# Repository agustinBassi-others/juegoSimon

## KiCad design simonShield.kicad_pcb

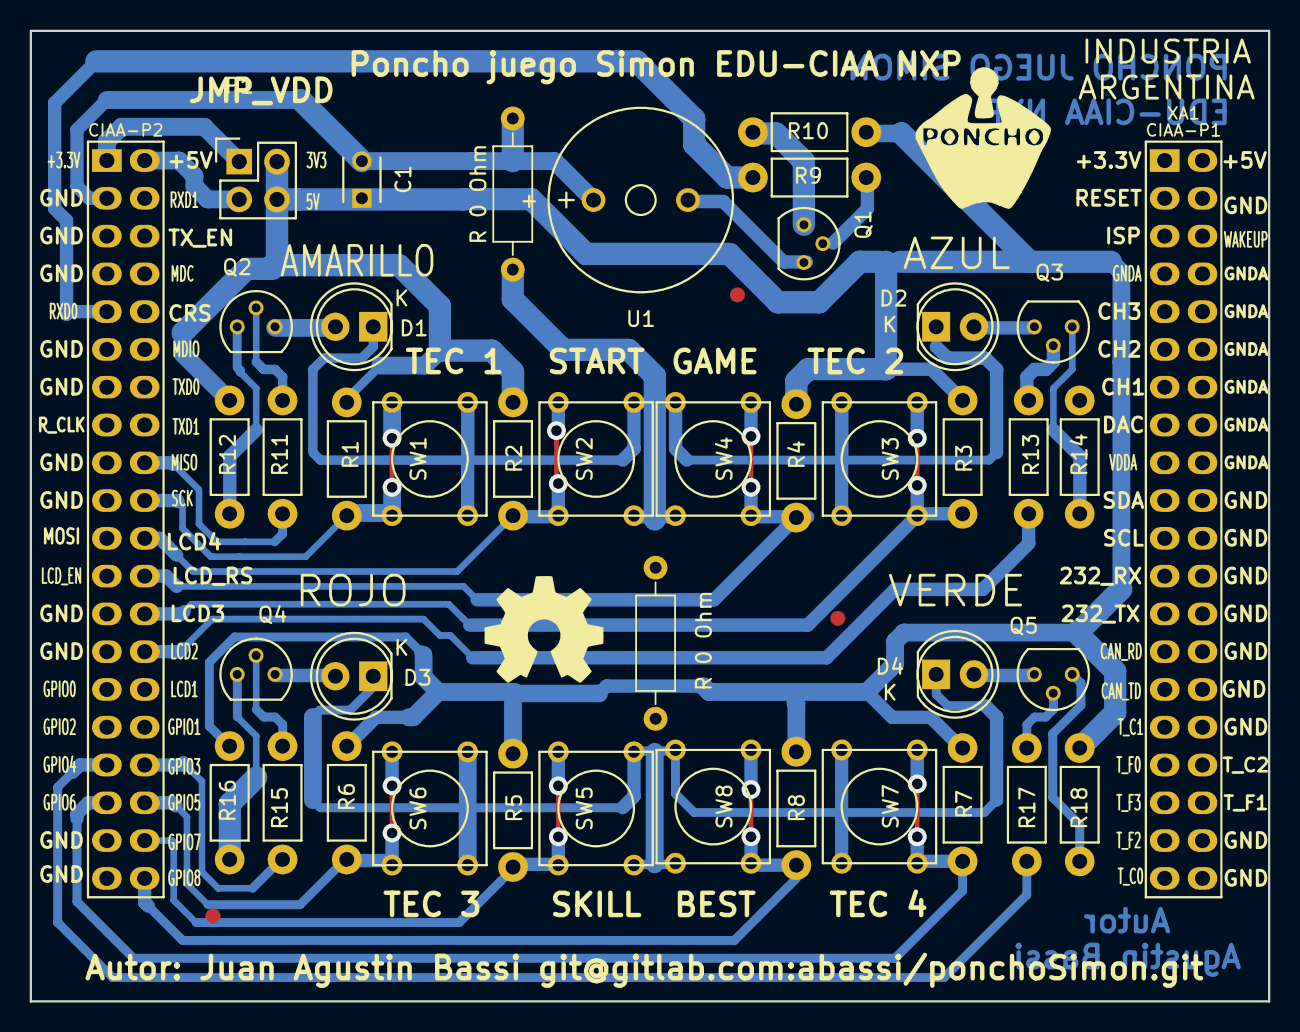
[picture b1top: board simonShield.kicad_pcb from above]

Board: 2 copper layers, 83.2 x 65.2 mm, 45 parts (0 on the bottom side), 32 nets.

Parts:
C1: C_100nF; C_Disc_D3_P2.5
D1: AMARILLO; LED-5MM
D2: AZUL; LED-5MM
D3: ROJO; LED-5MM
D4: VERDE; LED-5MM
F1, F2, F3: FIDUCIAL; Fiducial_1mm
G101: Logo_OSHWA
P1: PWR_JUMPER; Pin_Header_Straight_2x02
Q1, Q2, Q3, Q4, Q5: BC547; TO-92_Molded_Narrow
R1, R2, R3, R4, R5, R6, R7, R8, R9: 3K3; Resistor_Horizontal_RM7mm
R10: 1K; Resistor_Horizontal_RM7mm
R11, R13, R15, R17: 10K; Resistor_Horizontal_RM7mm
R12, R14, R16, R18: 680; Resistor_Horizontal_RM7mm
R 0 Ohm, R 0 Ohm#2: R; R_Axial_DIN0207_L6.3mm_D2.5mm_P10.16mm_Horizontal
SW1, SW2, SW3, SW4, SW5, SW6, SW7, SW8: SW_PUSH; SW_PUSH_SMALL
U1: BUZZER; MagneticBuzzer_ProSignal_ABT-410-RC
XA1: Conn_Poncho2P_2x_20x2; Conn_Poncho_SinBorde

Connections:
/buttons/BTN_CFG_1: R2.1, SW2.1, XA1.62
/buttons/BTN_CFG_2: R4.1, SW4.1, XA1.64
/buttons/BTN_CFG_3: R6.1, SW6.1, XA1.76
/buttons/BTN_CFG_4: R8.1, SW8.1, XA1.80
/buttons/BTN_LED_1: R1.1, SW1.1, XA1.60
/buttons/BTN_LED_2: R3.1, SW3.1, XA1.66
/buttons/BTN_LED_3: R5.1, SW5.1, XA1.78
/buttons/BTN_LED_4: R7.1, SW7.1, XA1.75
/ciaaConector/LED_1: R11.1, XA1.58
/ciaaConector/LED_2: R13.1, XA1.68
/ciaaConector/LED_3: R15.1, XA1.74
/ciaaConector/LED_4: R17.1, XA1.73
/ciaaConector/PWM: R9.2, XA1.49
GND: C1.2, D1.1, D2.1, D3.1, D4.1, R 0 Ohm.1, R 0 Ohm.2, R 0 Ohm#2.1, R 0 Ohm#2.2, SW1.2, SW2.2, SW3.2, SW4.2, SW5.2, SW6.2, SW7.2, SW8.2, U1.2, XA1.43, XA1.77, XA1.79
unnamed: D1.2, Q2.3
unnamed: D2.2, Q3.3
unnamed: D3.2, Q4.3
unnamed: D4.2, Q5.3
unnamed: P1.1, XA1.41
unnamed: P1.3, XA1.42
unnamed: Q1.1, R10.2
unnamed: Q1.2, R9.1
unnamed: Q1.3, U1.1
unnamed: Q2.1, R12.1
unnamed: Q2.2, R11.2
unnamed: Q3.1, R14.1
unnamed: Q3.2, R13.2
unnamed: Q4.1, R16.1
unnamed: Q4.2, R15.2
unnamed: Q5.1, R18.1
unnamed: Q5.2, R17.2
VCC: C1.1, P1.2, P1.4, R1.2, R2.2, R3.2, R4.2, R5.2, R6.2, R7.2, R8.2, R10.1, R12.2, R14.2, R16.2, R18.2

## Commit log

2017-07-01 Version 1 practicamente terminada de poncho Simon con EDU CIAA.
2017-07-01 Version luego de cambiar los pines y agregar dos resistencias de puentes.@
2017-07-01 Version totalmente ruteada. Previo a hacer puentes con resistencia y a serigrafia.
2017-07-01 Commit de acomodo de directorio. Previo a generar los gerbers de fabricacion final.
2017-07-01 Version final de la feature del Poncho Simon para realizarlo con la plancha.
2017-07-07 Acomodo del directorio agregando la carpeta firmware, case y doc.
2017-07-07 Agrega los nuevos archivos de firmware y agrega toda la carpeta hard.
2017-07-08 Primera Version usable en HW. Cambio de pin TECLA_AMARILLO. Tecla SKILL y ROJA detectadas iguales.
2017-07-08 Segunda version usable. Estados definidos y funcionalidad de delay con skill funcionando.
2019-05-14 Acomoda los tabs del codigo fuente.
